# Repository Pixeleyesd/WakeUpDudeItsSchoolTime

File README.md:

# WakeUpDudeItsSchoolTime
WakeUpDudeItsSchoolTime is an alarm clock with 6 keys, a TFT screen and a buzzer (to make the alarm sounds ofc)

## Features
- Time is automatically synced with Wi-Fi
- Allows up to 5 alarms at a time
- Configurations saved to system memory
- Different themes
- Time zone support, with manual daylight savings toggle

## CAD Design
I used OnShape to design my 3D model. The top and bottom are secured with screws to keep everything sturdy.

This simple design comprises of 2 seperate parts. The main shell used for holding the PCB and all of the keys, and the cover. [Onshape Link](https://cad.onshape.com/documents/61f7fc762917904c003c24e4/w/2d7d6437887083c7ad1da611/e/ae8d4ad74be62245f16cf310?renderMode=0&uiState=6acc61c17a0076c403724d2a)

## PCB Design
The PCB was designed using KiCad. I had to wire BL directly to GND and RST to +3.3V in order to allow enough pins for my 6 buttons.

## Firmware
#### PLEASE NOTE, IT IS RECOMMENDED TO REPLACE THE WIFI SSID IN THE FIRMWARE WITH YOUR OWN.

WakeUpDudeItsSchoolTime uses firmware written in C++.

Below is the layout of the switches:
```
SW1  SW3  SW5

SW2  SW4  SW6
```

- SW1 is `select / menu`
- SW2 is `back / cancel`
- SW3 is `up`
- SW4 is `down`
- SW5 is `alarm menu`
- SW6 is `sleep`

When you first boot up, it first asks you for your time zone (you enter the value to add to gmt), then it asks whether daylight savings applies. These customisations are saved to the internal memory. The alarm clock will show time on the main screen. You can add alarms by going into the menu, or by pressing the alarm menu hotkey (SW5). Once power cycled, it will not keep the time, but uses WIFI to resync time using the internet.

## Bill of Materials (BOM)
Here is everything you will need to build WakeUpDudeItsSchoolTime:

- 1x Seeed XIAO ESP32C3
- 6x MX-Style Keyboard Switches
- 6x White Blank DSA Keycaps
- 1x 2.25in TFT Screen
- 1x 3.3V Piezo Buzzer
- 1x 2.54mm 8 Pin Male Header (For connecting your screen)
- 8x 20cm Female-Female Jumper Wires (For connecting your screen off of the pcb)
- 8x M3x5x4 Heatset Inserts
- 4x M3x8mm Screws
- 4x M3x16mm Screws

---

This is the second time I've used KiCAD for PCB design and my first time designing an alarm clock like this. I've learned a lot from this project. Thanks to the Hackclub (and Stardance) team for providing these amazing resources that helped make this dream of mine come true.

Here is the guide I followed. [Link](https://blare.hackclub.com/index.html)

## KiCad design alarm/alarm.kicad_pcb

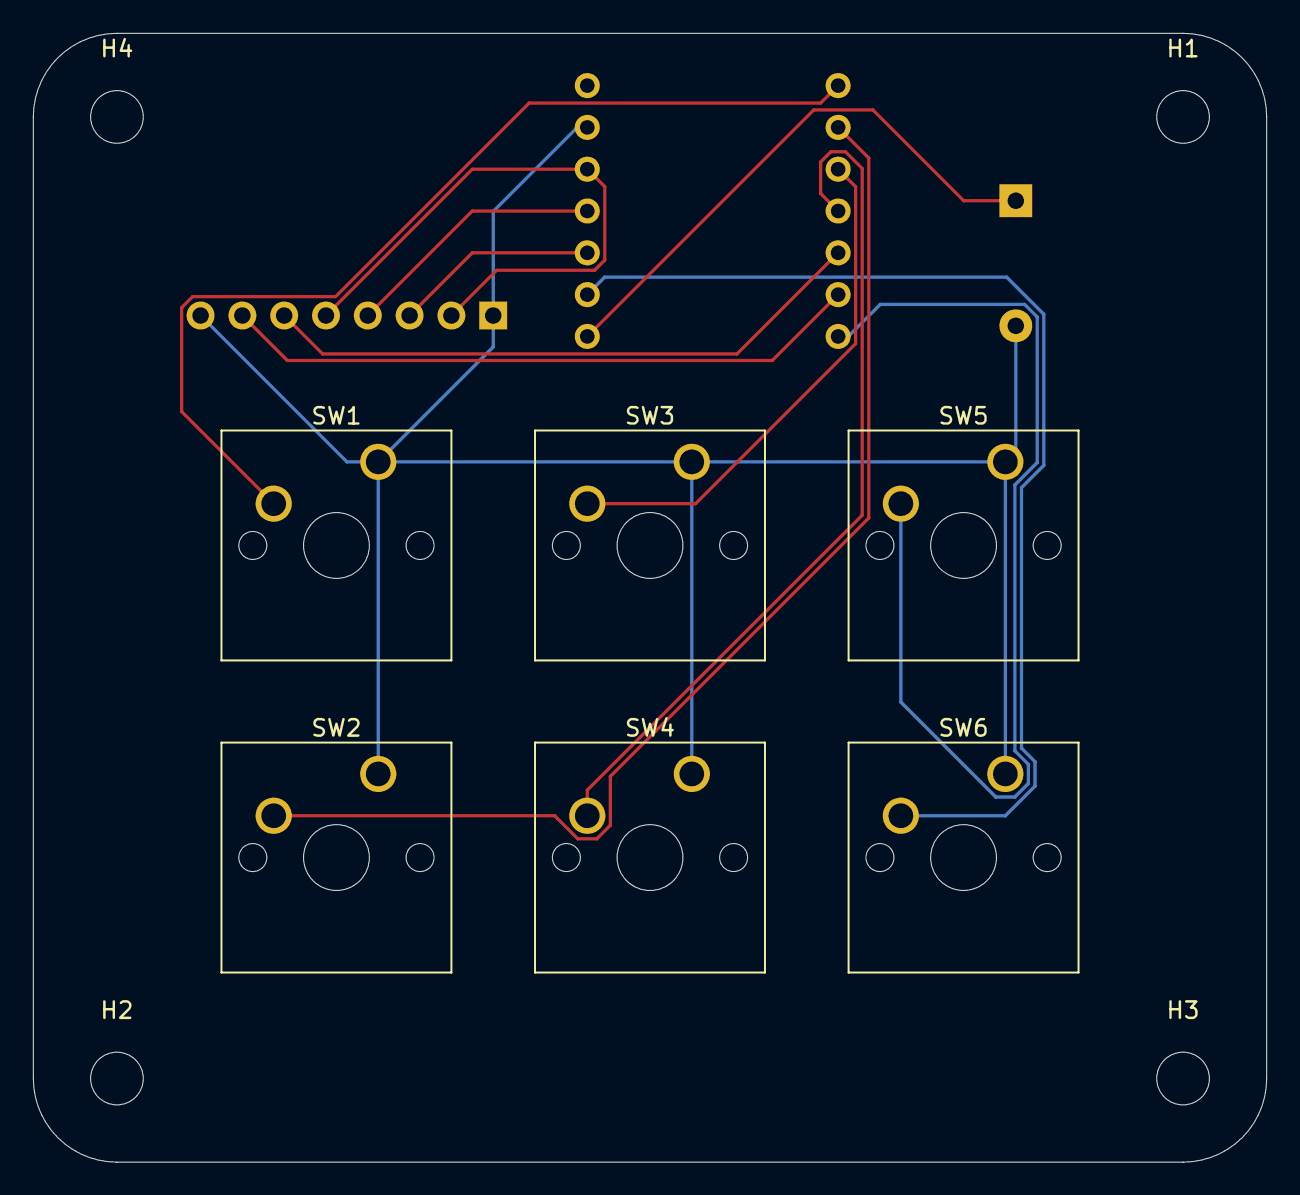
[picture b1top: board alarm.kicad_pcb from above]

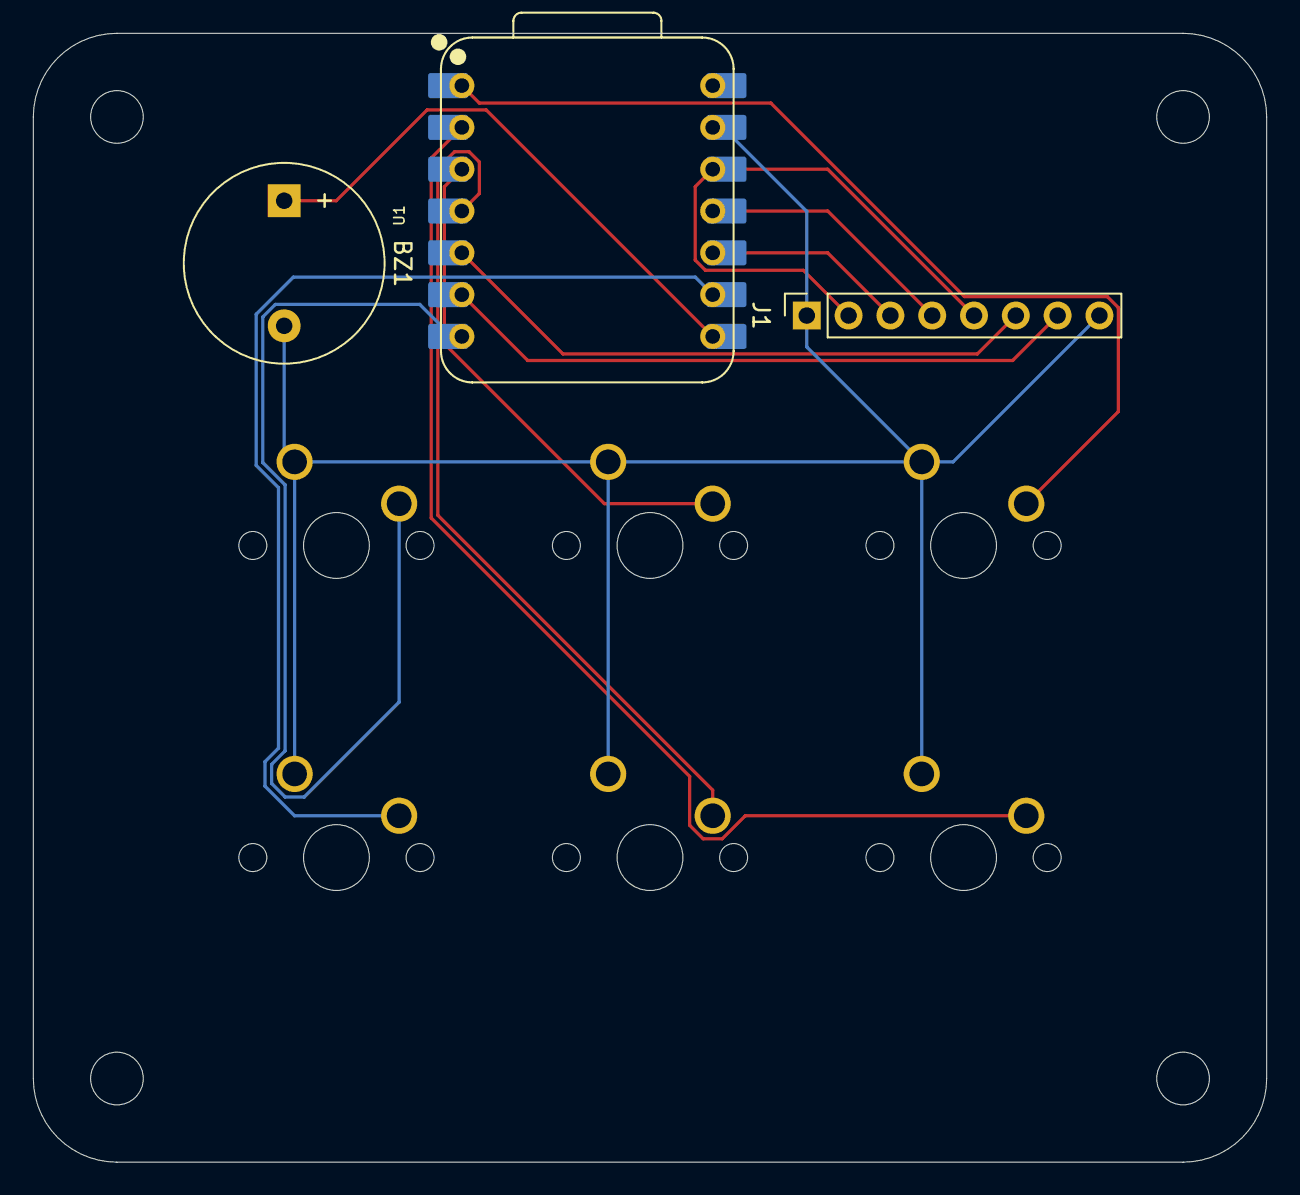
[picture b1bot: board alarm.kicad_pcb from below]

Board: 2 copper layers, 74.9 x 68.6 mm, 13 parts (3 on the bottom side), 13 nets.

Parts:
BZ1: Buzzer; Buzzer_12x9.5RM7.6
H1, H2, H3, H4: MountingHole; MountingHole_3.2mm_M3
J1: Conn_01x08_Pin; PinSocket_1x08_P2.54mm_Vertical
SW1, SW2, SW3, SW4, SW5, SW6: SW_Push; SW_Cherry_MX_1.00u_PCB
U1: XIAO-ESP32-C3-SMD; XIAO-ESP32-C3-DIP

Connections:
+3.3V: J1.2, J1.5, U1.12 (3V3_OUT)
GND: BZ1.2 (-), J1.1, J1.8, SW1.1, SW2.1, SW3.1, SW4.1, SW5.1, SW6.1, U1.13 (GND)
unnamed: BZ1.1 (+), U1.8 (D7)
unnamed: J1.3, U1.10 (D9/BOOT)
unnamed: J1.4, U1.11 (D10)
unnamed: J1.6, U1.5 (D4)
unnamed: J1.7, U1.6 (D5)
unnamed: SW1.2, U1.1 (D0)
unnamed: SW2.2, U1.2 (D1)
unnamed: SW3.2, U1.3 (D2)
unnamed: SW4.2, U1.4 (D3)
unnamed: SW5.2, U1.7 (D6)
unnamed: SW6.2, U1.9 (D8)
